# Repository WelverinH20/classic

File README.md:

# akkotako67

A 65% keyboard with WS2812B rgb LED strips for underglow and two rotary encoders.

This keyboard uses an Elite-C microcontroller for the keyboard with LED lights and rotary encoders.

The layout was designed using keyboard-layout-editor.com, with the KiCad project file produced by keyboard-tools.xyz. All modifications to the PCB were made in KiCad 7.0. Please see git history for the keyboard's progress.

This keyboard was designed and manufactured by Sofia McNary, Colton Yates, Sam Warr, Kevin James, and Brandon Flexman.

This model does not have traces. This PCB model has nets and components, and is meant for tutorials in how to design PCBs using KiCad for the 2024-2025 BYU IEEE student branch project.

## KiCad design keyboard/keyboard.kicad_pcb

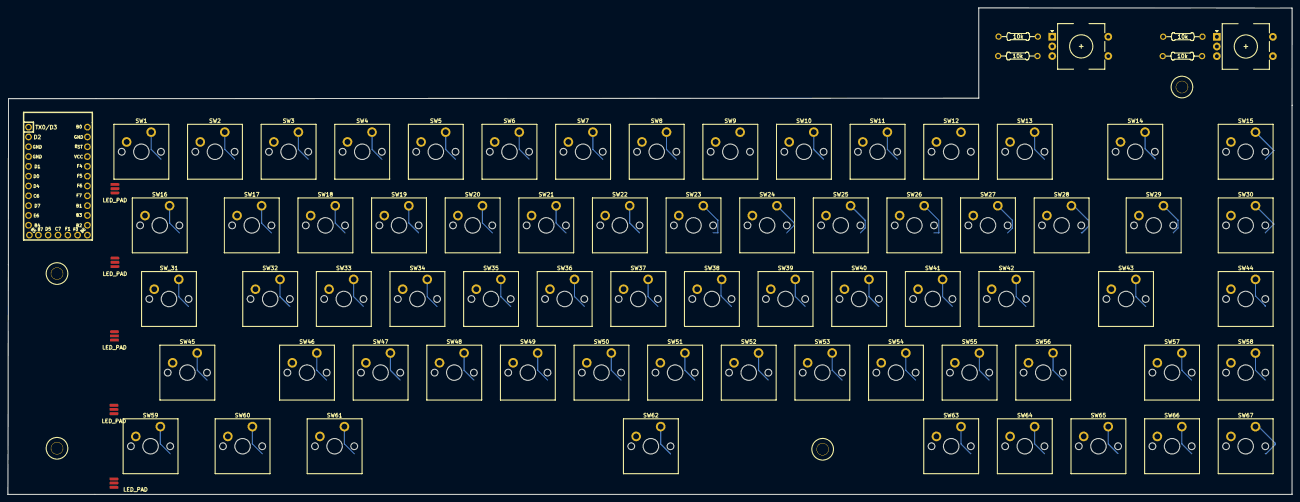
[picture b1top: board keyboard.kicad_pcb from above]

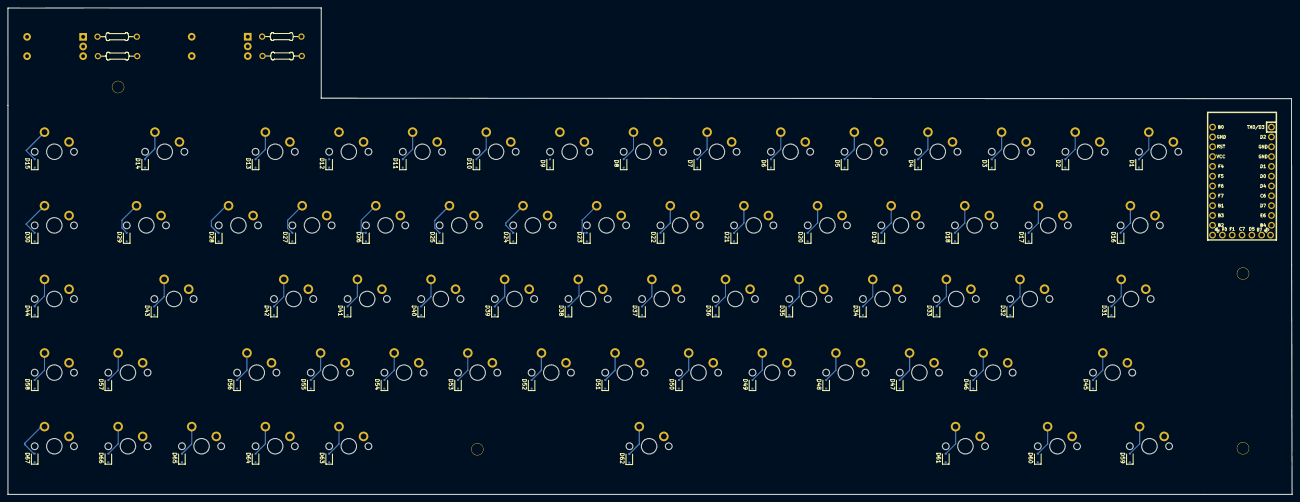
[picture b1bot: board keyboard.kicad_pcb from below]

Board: 2 copper layers, 332.3 x 125.9 mm, 149 parts (67 on the bottom side), 67 nets.

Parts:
D1, D2, D3, D4, D5, D6, D7, D8, D9, D10, D11, D12, D13, D14, D15, D16, D17, D18, D19, D20, D21, D22, D23, D24, D25, D26, D27, D28, D29, D30, D31, D32, D33, D34, D35, D36, D37, D38, D39, D40, D41, D42, D43, D44, D45, D46, D47, D48, D49, D50, D51, D52, D53, D54, D55, D56, D57, D58, D59, D60, D61, D62, D63, D64, D65, D66, D67: D; D_SOD-323F
EC11_Rotary_Encoder, EC11_Rotary_Encoder#2: RotaryEncoder_EC11
LED_PAD: WS2812B SMD Strip 3mm
LED_PAD#2, LED_PAD#3, LED_PAD#4: WS2812B SMD Strip 3mm
Ref**: 10k; Resistor
Ref**#2, Ref**#3, Ref**#4: 10k; Resistor
SW1, SW2, SW3, SW4, SW5, SW6, SW7, SW8, SW9, SW10, SW11, SW12, SW13, SW15, SW17, SW18, SW19, SW20, SW21, SW22, SW23, SW24, SW25, SW26, SW27, SW28, SW30, SW32, SW33, SW34, SW35, SW36, SW37, SW38, SW39, SW40, SW41, SW42, SW44, SW46, SW47, SW48, SW49, SW50, SW51, SW52, SW53, SW54, SW55, SW56, SW57, SW58, SW63, SW64, SW65, SW66, SW67: SW_Push; SW_Cherry_MX_PCB_1.00u
SW14: SW_Push; SW_Cherry_MX_PCB_2.00u
SW16, SW29: SW_Push; SW_Cherry_MX_PCB_1.50u
SW43, SW45: SW_Push; SW_Cherry_MX_PCB_2.25u
SW59, SW60, SW61: SW_Push; SW_Cherry_MX_PCB_1.25u
SW62: SW_Push; SW_Cherry_MX_PCB_6.25u
SW_31: SW_Push; SW_Cherry_MX_PCB_1.75u
U1: Elite-C
U4, U4#2, U4#3, U4#4: HOLE; MountingHole

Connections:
unnamed: D1.2, SW1.2
unnamed: D2.2, SW2.2
unnamed: D3.2, SW3.2
unnamed: D4.2, SW4.2
unnamed: D5.2, SW5.2
unnamed: D6.2, SW6.2
unnamed: D7.2, SW7.2
unnamed: D8.2, SW8.2
unnamed: D9.2, SW9.2
unnamed: D10.2, SW10.2
unnamed: D11.2, SW11.2
unnamed: D12.2, SW12.2
unnamed: D13.2, SW13.2
unnamed: D14.2, SW14.2
unnamed: D15.2, SW15.2
unnamed: D16.2, SW16.2
unnamed: D17.2, SW17.2
unnamed: D18.2, SW18.2
unnamed: D19.2, SW19.2
unnamed: D20.2, SW20.2
unnamed: D21.2, SW21.2
unnamed: D22.2, SW22.2
unnamed: D23.2, SW23.2
unnamed: D24.2, SW24.2
unnamed: D25.2, SW25.2
unnamed: D26.2, SW26.2
unnamed: D27.2, SW27.2
unnamed: D28.2, SW28.2
unnamed: D29.2, SW29.2
unnamed: D30.2, SW30.2
unnamed: D31.2, SW_31.2
unnamed: D32.2, SW32.2
unnamed: D33.2, SW33.2
unnamed: D34.2, SW34.2
unnamed: D35.2, SW35.2
unnamed: D36.2, SW36.2
unnamed: D37.2, SW37.2
unnamed: D38.2, SW38.2
unnamed: D39.2, SW39.2
unnamed: D40.2, SW40.2
unnamed: D41.2, SW41.2
unnamed: D42.2, SW42.2
unnamed: D43.2, SW43.2
unnamed: D44.2, SW44.2
unnamed: D45.2, SW45.2
unnamed: D46.2, SW46.2
unnamed: D47.2, SW47.2
unnamed: D48.2, SW48.2
unnamed: D49.2, SW49.2
unnamed: D50.2, SW50.2
unnamed: D51.2, SW51.2
unnamed: D52.2, SW52.2
unnamed: D53.2, SW53.2
unnamed: D54.2, SW54.2
unnamed: D55.2, SW55.2
unnamed: D56.2, SW56.2
unnamed: D57.2, SW57.2
unnamed: D58.2, SW58.2
unnamed: D59.2, SW59.2
unnamed: D60.2, SW60.2
unnamed: D61.2, SW61.2
unnamed: D62.2, SW62.2
unnamed: D63.2, SW63.2
unnamed: D64.2, SW64.2
unnamed: D65.2, SW65.2
unnamed: D66.2, SW66.2
unnamed: D67.2, SW67.2

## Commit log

2024-10-10 Added files for keyboard
2024-10-10 Updated keyboard project files
2024-10-10 Removed nets and traces from keyboard
2024-10-10 started working on traces,
    Im not 100% on the pcb design so I may go into ergogen and mess around with it
2024-10-12 Great is the name RatsNest
    Worked on creating a rats nest for the keyboard. im trying to figure out if I want to use an esp 32 or elite-c controller. Im leaning towards esp32 for more power but we will see if I can find a kica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
2024-12-11 added qmk archive
